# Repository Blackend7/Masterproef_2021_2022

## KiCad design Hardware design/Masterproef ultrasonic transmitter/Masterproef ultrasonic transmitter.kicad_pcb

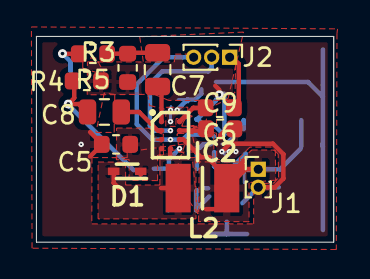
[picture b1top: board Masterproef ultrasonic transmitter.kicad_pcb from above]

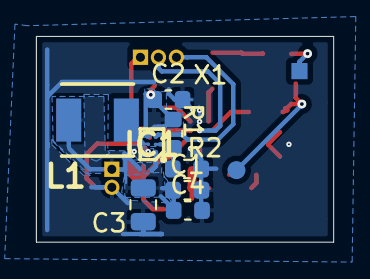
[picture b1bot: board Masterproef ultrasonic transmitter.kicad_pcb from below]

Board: 2 copper layers, 16.5 x 11.4 mm, 22 parts (9 on the bottom side), 17 nets.

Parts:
C1, C4, C5, C6, C9: 1µF; C_0603_1608Metric
C2: 2,2µF; C_0603_1608Metric
C3, C7, C8: 10µF; C_0805_2012Metric
D1: NSR0520V2T1G; SODFL1608X70N
IC1: TPS61046YFFR; BGA6C40P2X3_79X119X62
IC2: LM48580TL_NOPB; BGA12C50P3X4_146X196X68
J1: Power; PinHeader_1x02_P1.00mm_Vertical
J2: Control; PinHeader_1x03_P1.00mm_Vertical
L1: FDSD0420-H-100M=P3; FDSD0420WH150MP3
L2: BRL3225T4R7M; INDC3225X170N
R1: 536k; R_0603_1608Metric
R2: 30k; R_0603_1608Metric
R3, R4: 100k; R_0603_1608Metric
R5: 10; R_0603_1608Metric
X1: Adap_UT_P2019

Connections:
+3V3: C1.1, C3.1, C4.1, IC1.A1, IC2.C3, J1.1, L1.1, L2.2
+15V: C2.1, IC1.C2, R1.1, R3.2, R4.2
/AUDIO_IN: C6.1, J2.1
/ENABLE: IC1.C1, IC2.C2, J2.3
/GAIN: IC2.B2, J2.2
/MEMS_NEG_POLE: C8.1, R4.1, X1.2
/MEMS_POS_POLE: R5.2, X1.1
GND: C1.2, C2.2, C3.2, C4.2, C5.2, C9.2, IC1.A2, IC2.A2, IC2.D3, J1.2, R2.2
unnamed: C5.1, D1.1, IC2.C1, IC2.D1
unnamed: C6.2, IC2.A3
unnamed: C7.1, R3.1, R5.1
unnamed: C7.2, IC2.A1
unnamed: C8.2, IC2.B1
unnamed: C9.1, IC2.B3
unnamed: D1.2, IC2.D2, L2.1
unnamed: IC1.B1, R1.2, R2.1
unnamed: IC1.B2, L1.2

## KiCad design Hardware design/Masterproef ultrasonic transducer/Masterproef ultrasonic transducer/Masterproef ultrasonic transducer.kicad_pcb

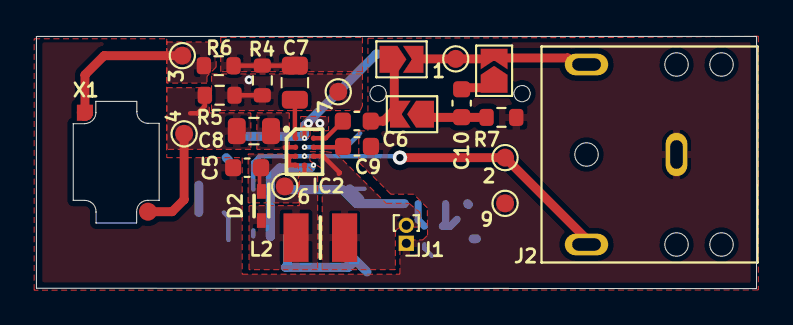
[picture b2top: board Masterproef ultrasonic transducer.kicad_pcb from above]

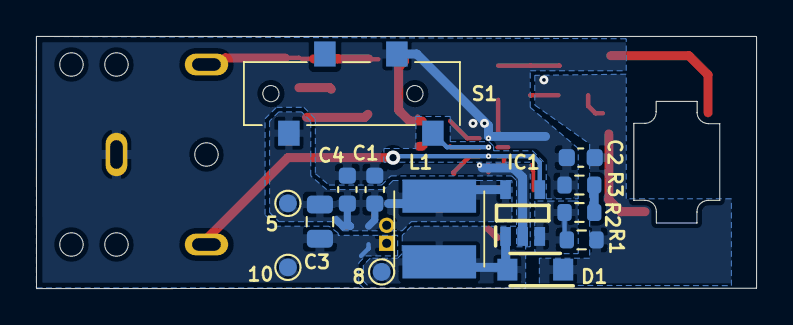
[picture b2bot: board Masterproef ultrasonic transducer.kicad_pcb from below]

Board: 2 copper layers, 40.0 x 14.0 mm, 40 parts (14 on the bottom side), 21 nets.

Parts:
1: Audio; TestPoint_Pad_D1.0mm
2: Enable; TestPoint_Pad_D1.0mm
3: MEMS_POS_POLE; TestPoint_Pad_D1.0mm
4: MEMS_NEG_POLE; TestPoint_Pad_D1.0mm
5: VCC; TestPoint_Pad_D1.0mm
6: VBST; TestPoint_Pad_D1.0mm
7: +15V; TestPoint_Pad_D1.0mm
8: SW; TestPoint_Pad_D1.0mm
9, 10: GND; TestPoint_Pad_D1.0mm
C1: 10µF; C_0603_1608Metric
C2, C10: 2,2µF; C_0603_1608Metric
C3: 10µF; C_0805_2012Metric
C4, C5, C6, C9: 1µF; C_0603_1608Metric
C7, C8: 1µF; C_0805_2012Metric
D1: SS22FA; SODFL3618X143N
D2: PMEG2010AEB,115; SOD1608X65N
IC1: MIC2251-2YD5-TR; SOT95P280X100-5N
IC2: LM48580TL_NOPB; BGA12C50P3X4_146X196X68
J1: Power; PinHeader_1x02_P1.00mm_Vertical
J2: FC68131; CLIFF_FC68131
JP1: no filter; SolderJumper-2_P1.3mm_Open_TrianglePad1.0x1.5mm
JP2, JP3: input filter; SolderJumper-2_P1.3mm_Open_TrianglePad1.0x1.5mm
L1: LQH5BPN100MT0L; LQH5BPB100MT0L
L2: BRL3225T4R7M; INDC3225X170N
R1: 1M; R_0603_1608Metric
R2: 68k; R_0603_1608Metric
R3: 22k; R_0603_1608Metric
R4, R5: 10k; R_0603_1608Metric
R6: 10; R_0603_1608Metric
R7: 4,7; R_0603_1608Metric
S1: CL-SB-13B-01T; CLSB13B01T
X1: Adap_UT_P2019

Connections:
+3V3: 5.1, C1.1, C3.1, C4.1, IC1.5, IC2.C3, J1.2, L1.1, L2.1, S1.4
+15V: 7.1, C2.1, D1.1, R1.1, R4.2, R5.2
/AUDIO_IN: 1.1, J2.5, JP1.2, JP2.2
/ENABLE: 2.1, IC1.4, IC2.C2, J2.2
/GAIN: IC2.B2, S1.3
/MEMS_NEG_POLE: 4.1, C8.1, R5.1, X1.2
/MEMS_POS_POLE: 3.1, R6.2
GND: 9.1, 10.1, C1.2, C2.2, C3.2, C4.2, C5.2, C9.2, IC1.2, IC2.A2, IC2.D3, J1.1, J2.1, R3.1, R7.1, S1.1
unnamed: 6.1, C5.1, D2.1, IC2.C1, IC2.D1
unnamed: C6.1, JP1.1, JP3.2
unnamed: C6.2, IC2.A3
unnamed: C7.1, R4.1, R6.1
unnamed: C7.2, IC2.A1
unnamed: C8.2, IC2.B1
unnamed: C9.1, IC2.B3
unnamed: C10.1, JP2.1
unnamed: C10.2, JP3.1, R7.2
unnamed: 8.1, D1.2, IC1.1, L1.2
unnamed: D2.2, IC2.D2, L2.2
unnamed: IC1.3, R1.2, R2.2
unnamed: R2.1, R3.2

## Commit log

2022-01-28 Thesis ingediend
